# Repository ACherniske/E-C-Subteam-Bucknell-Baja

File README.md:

# E&C Subteam Documentation Bucknell Baja Car
Wiring Harness, Controls, and Data Aquisition work for Bucknell Baja Electronics and Controls Subteam

------------------------------------------------------------------
<details>
<summary> Background </summary>

## What is Baja SAE?
Baja SAE is a globally recognized engineering competition hosted by SAE International, where university teams design, build, and test single-seat, off-road vehicles. These vehicles must endure rugged terrain and demonstrate capabilities in traction, stability, endurance, and maneuverability.

The Baja SAE competition emphasizes practical engineering skills, teamwork, and project management as students navigate the real-world challenges of designing, manufacturing, and testing a functional, durable vehicle. Participants engage in all stages of vehicle development, from concept to fabrication, while adhering to competition guidelines and safety requirements.

Teams compete in various events, including acceleration, hill climbs, and a grueling endurance race that tests the vehicle’s reliability over long distances. The competition allows engineering students to apply and expand their knowledge in areas like mechanical design, electronics, and control systems—developing crucial skills for their future careers.

[**Official Rulebook**](BAJA_RULES_2024_Rev_A_2023-08-31.pdf)  

</details>

## Scope

This documentation provides an overview of the **Electronics and Controls** systems implemented in our Baja SAE vehicle, in accordance with relevant sections of the Baja SAE 2024 rulebook. The systems described here prioritize safety, reliability, and regulatory compliance, ensuring that all electronic and control functionalities meet competition standards. Our scope specifically includes the following components:

- **Electrical System** (B.10): The vehicle includes a minimum electrical setup as required by rule B.10, encompassing dual engine kill switches, a brake light, and a main battery for system power. All safety and signaling systems are designed to function independently of the kill switches to maintain continuous operation during vehicle shutdowns.

- **Battery Requirements** (B.10.1.1):
  - **Mounting and Sealing**: We selected and mounted a factory-sealed, maintenance-free battery that remains securely fixed during normal operation and under collision forces, as specified in B.10.1.1.1.
  - **Capacity**: For systems powered by this battery, we conducted capacity assessments to confirm reliable performance throughout the event, fulfilling rule B.10.1.1.3.

- **Wiring and Connectors** (B.10.2): All wiring is routed to avoid high-temperature or high-wear areas, supporting accessibility and maintaining safety per B.10.2. Wiring pathways are designed to prevent interference with driver egress and other critical components.

- **Kill Switches** (B.10.3): In compliance with B.10.3, the vehicle has two kill switches for engine cutoff—one within the driver’s reach in the cockpit and an external one accessible for track workers. Both are firmly mounted and ensure instant engine shutdown during emergency stops.

- **Signaling Devices** (B.10.4):
  - **Brake Light**: The vehicle uses an approved brake light positioned for visibility to trailing drivers, activated exclusively by a hydraulic pressure switch on the brake system, as outlined in rule B.10.4.1.

- **Data Acquisition** (B.10.6): The vehicle is equipped with optional data acquisition systems to log performance metrics. These systems do not relay real-time feedback to the driver, and all associated costs are included in the official competition cost report.

This document will evolve as we continue refining the Electronics and Controls subsystems to ensure both safety and competitive performance within Baja SAE specifications.

## Project Subpages

- [Wiring Harness](/Projects/WiringHarness/WiringHarness.md)
- [Data Logger](/Projects/DataLogger/DataLogger.md)
- [Differential](/Projects/Differential/Differential.md)

## Future Updates
-Front and Rear Diff Wiring (in testing)
-DAQ Breakout Board (delayed)

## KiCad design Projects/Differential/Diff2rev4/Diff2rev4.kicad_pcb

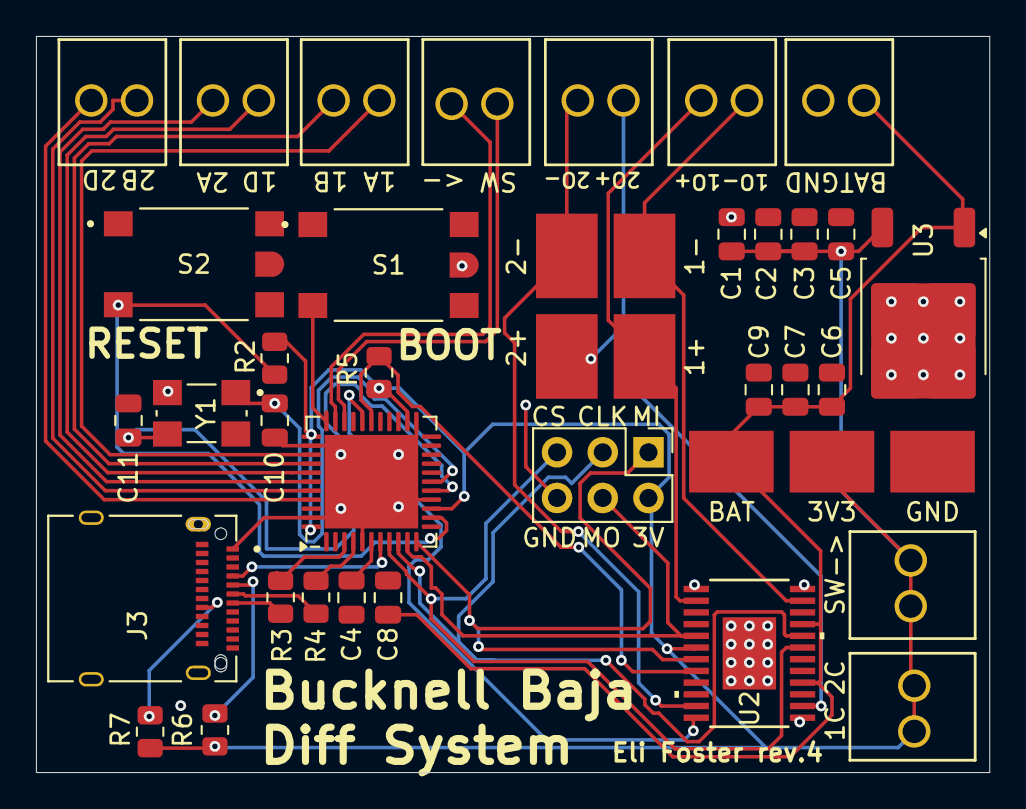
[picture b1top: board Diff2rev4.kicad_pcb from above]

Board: 2 copper layers, 53.0 x 40.9 mm, 42 parts (0 on the bottom side), 33 nets.

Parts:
1+, 1-, 2+, 2-, 3V3: 5016; KEYSTONE_5016
BAT: 5016; KEYSTONE_5016
C1, C5, C6, C7, C8: 0.1uF; C_0805_2012Metric
C2, C9: 10uF; C_0805_2012Metric
C3, C4: 1uF; C_0805_2012Metric
C10, C11: 36pF; C_0805_2012Metric
GND: 5016; KEYSTONE_5016
Image1: Baja; bajabig
J1: AVR-ISP-6; PinHeader_2x03_P2.54mm_Vertical
J3: 12401598E4_2A; AMPHENOL_USBC
R2, R5, R6, R7: 10k; R_0805_2012Metric
R3, R4: 22; R_0805_2012Metric
S1, S2: FSM1LPATR; SW_1-1437565-8
Switches_In1: OSTVN02A150; CONN_OSTVN02A150_OST
Switches_Out1: OSTVN02A150; CONN_OSTVN02A150_OST
Terminal_1Out1, Terminal_2Out1: OSTVN02A150; CONN_OSTVN02A150_OST
Terminal_C1: OSTVN02A150; CONN_OSTVN02A150_OST
Terminal_In1, Terminal_In2, Terminal_In3: OSTVN02A150; CONN_OSTVN02A150_OST
Terminal_PowerIn1: OSTVN02A150; CONN_OSTVN02A150_OST
U1: ATmega32U4-M; QFN-44-1EP_7x7mm_P0.5mm_EP5.2x5.2mm
U2: DRV8904QPWPRQ1; HTSSOP24_PWP_TEX
U3: AP7363-33D-13; TO-252-2
Y1: C5S-24.000-20-3030-X-R; XTAL_C5S-24.000-20-3030-X-R

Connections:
3V: 3V3.TP, C1.1, C2.1, C3.1, C5.1, J1.2 (VCC), R2.2, R5.1, R6.2, R7.2, Switches_Out1.1, Switches_Out1.2, Terminal_C1.1, Terminal_C1.2, U1.14 (VCC), U1.24 (AVCC), U1.34 (VCC), U1.44 (AVCC), U2.6 (VDD), U3.3 (OUT)
+BATT: BAT.TP, C6.1, C7.1, C8.1, C9.1, Terminal_PowerIn1.1, U2.16 (VM), U2.21 (VM), U3.1 (IN)
ATM_UDM: R3.2, U1.3 (D-)
ATM_UDP: R4.2, U1.4 (D+)
BOOTLOADER: S1.3, U1.33 (~HWB/PE2)
CLK: J1.3 (SCK), U1.9 (PB1), U2.20 (SCLK)
CS: J1.5 (~RST), U1.8 (PB0), U2.19 (NSCS)
DIFF1+: 1+.TP, Terminal_1Out1.2, U2.2 (OUT1)
DIFF1-: 1-.TP, Terminal_1Out1.1, U2.23 (OUT2)
DIFF1A: Terminal_In1.1, U1.36 (PF7)
DIFF1B: Terminal_In1.2, U1.37 (PF6)
DIFF1D: Terminal_In2.1, U1.38 (PF5)
DIFF2+: 2+.TP, Terminal_2Out1.1, U2.14 (OUT3)
DIFF2-: 2-.TP, Terminal_2Out1.2, U2.11 (OUT4)
DIFF2A: Terminal_In2.2, U1.39 (PF4)
DIFF2B: Terminal_In3.1, U1.40 (PF1)
DIFF2D: Terminal_In3.2, U1.41 (PF0)
MISO: J1.1 (MISO), U1.11 (PB3), U2.7 (SDO)
MOSI: J1.4 (MOSI), U1.10 (PB2), U2.5 (SDI)
NFAULT: U1.29 (PB5), U2.12 (NFAULT)
NSLEEP: R5.2, U1.28 (PB4), U2.8 (NSLEEP)
unnamed: J3.A5 (CC1), R6.1
unnamed: J3.B5 (CC2), R7.1
RESET_SW: R2.1, S2.3, U1.13 (~RESET)
SW1_IN: Switches_In1.2, U1.31 (PC6)
SW2_IN: Switches_In1.1, U1.32 (PC7)
UCAP: C4.1, U1.6 (UCAP)
UGND: C1.2, C2.2, C3.2, C4.2, C5.2, C6.2, C7.2, C8.2, C9.2, C10.2, C11.2, GND.TP, J1.6 (GND), J3.A1 (GND), J3.SH1 (SHIELD), S1.1, S1.2, S1.4, S1.5 (SHIELD), S2.1, S2.2, S2.4, S2.5 (SHIELD), Terminal_PowerIn1.2, U1.5 (UGND), U1.15 (GND), U1.23 (GND), U1.35 (GND), U1.43 (GND), U1.45 (GND), U2.1 (GND), U2.13 (GND), U2.24 (GND), U2.EPAD (GND), U3.2 (GND), Y1.2 (GND), Y1.4 (GND__1)
USB_UDM: J3.A7 (DN1), R3.1
USB_UDP: J3.A6 (DP1), R4.1
USB_VBUS: J3.A4 (VBUS), U1.7 (VBUS)
XTAL1: C10.1, U1.17 (XTAL1), Y1.1
XTAL2: C11.1, U1.16 (XTAL2), Y1.3

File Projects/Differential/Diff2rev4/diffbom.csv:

Reference,Value,Datasheet,Footprint,Qty,DNP
"C1,C5,C6,C7,C8",0.1uF,~,Capacitor_SMD:C_0805_2012Metric,5,
"C2,C9",10uF,~,Capacitor_SMD:C_0805_2012Metric,2,
"C3,C4",1uF,~,Capacitor_SMD:C_0805_2012Metric,2,
"C10,C11",36pF,~,Capacitor_SMD:C_0805_2012Metric,2,
,,,,,
,,,,,
J3,12401598E4_2A,,custom:AMPHENOL_USBC,1,
"R2,R5,R6,R7",10k,~,Resistor_SMD:R_0805_2012Metric,4,
"R3,R4",22,~,Resistor_SMD:R_0805_2012Metric,2,
"S1,S2",FSM1LPATR,,custom:SW_1-1437565-8,2,
"Switches_In1,Switches_Out1,Terminal_1Out1,Terminal_2Out1,Terminal_C1,Terminal_In1,Terminal_In2,Terminal_In3,Terminal_PowerIn1",OSTVN02A150,OSTVN02A150,-- mixed values --,9,
"TP1,TP2,TP3,TP4,TP5,TP6,TP7",5016,,custom:KEYSTONE_5016,7,
U1,ATmega32U4-M,http://ww1.microchip.com/downloads/en/DeviceDoc/Atmel-7766-8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,Package_DFN_QFN:QFN-44-1EP_7x7mm_P0.5mm_EP5.2x5.2mm,1,
U2,DRV8904QPWPRQ1,DRV8904QPWPRQ1,custom:HTSSOP24_PWP_TEX,1,
U3,AP7363-33D-13,AP7363-33D-13,Package_TO_SOT_SMD:TO-252-2,1,
Y1,C5S-24.000-20-3030-X-R,,custom:XTAL_C5S-24.000-20-3030-X-R,1,

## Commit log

2024-11-25 Create Projects
2024-11-25 Rename wiring-harness.md to Projects/wiring-harness.md
2024-11-25 Rename datalogger.md to DAQ.md
2024-11-25 Rename wiring-harness.md to W-H.md
2025-03-07 DAQ Schematic
2025-03-07 DAW Schem jpg
2025-03-17 Add delay to recordData() so sensors will have a set interval
2025-03-17 formatting: Changing some formatting and adding some comments for clarity
2025-03-17 gitignore
2025-03-17 feat(): Docstring addition + Docstring outline for Aidan
2025-03-31 chore: Create folder and file for diff code
2025-03-31 chore: aiden is mean
2025-04-01 Wrote function for switch detection
2025-04-01 All Working Code exists in code.py at the moment and code2 is a working file for storing code that already works if code.py is needed for testing
2025-04-02 Wrote 2 new functions for testing at later date. Wrote docstrings for functions.
2025-04-02 Debug
2025-04-03 Logic works as expected for all currently tested conditions. Cannot drive motor from digital pin so an external hbridge or other solution will be needed.
2025-04-03 Working diff code and circuit
2025-04-04 Minor changes to code
2025-04-10 Updated Code
2025-04-10 Delete Projects/diff/code2.py
    removed redundant testing file
2025-04-12 File Structure Changes
2025-04-12 Updated File Structure and Md files
2025-04-12 File Structure Updates and Markdown
2025-04-12 File Name Correction
2025-04-12 Relative Links in README.md
2025-04-12 Formatting
2025-04-17 feat: Add H-Bridge Voltage Enable control D24
2025-07-02 Rev4 + models
2025-07-03 chore: clean kicad schematics
2025-11-05 create schematic
